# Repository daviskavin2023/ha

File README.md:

# 3038-网关-ha (Home Assistant 智能家居网关中心)

> 渔来喔智能家居体系核心网关。部署于 PVE 10 宿主机，通过 KVM 虚拟机运行 Home Assistant OS (HAOS)，实现对全屋开关、插座的集中管控、状态监控与高阶任务编排。

---

## 📌 项目定位

- **主控大脑**：Home Assistant 承担全屋逻辑控制、复杂任务编排、能源数据监控与跨协议桥接。
- **射频天线**：原**小米中枢网关**仅保留作为底层射频（Bluetooth Mesh / Zigbee）信号接收器，不参与任何上层自动化编排。
- **重点接管**：全屋智能开关（零火/单火、多键转无线）、智能计量插座（功率监测、电量统计）。

---

## 📁 目录结构

```text
3038-网关-ha/
├── PRD.md              # 产品与技术需求文档 (详细架构、避坑指南、配置规范)
├── README.md           # 项目速览与操作说明
└── docs/               # 部署命令、配置样例与自动化模板 (规划中)
```

---

## 🚀 核心架构与部署参数

- **宿主环境**：PVE 10 宿主机 (`10.10.10.10`)
- **虚拟机类型**：KVM (HAOS 官方 qcow2 镜像)
- **VM 规格**：
  - VM ID: `138` (名称: `haos-138`)
  - 固定 IP: `10.10.10.38/24`
  - 默认网关: `10.10.10.15` (旁路由)
  - DNS 服务器: `10.10.10.15` (旁路由)
  - BIOS: `OVMF (UEFI)`
  - Machine: `q35`
  - CPU: 2 vCPU (Type: `host`)
  - 内存: 4GB
  - 存储: 32GB ~ 64GB SSD (VirtIO SCSI Single, 开启 Discard)
  - 扩展特性: 开启 QEMU Guest Agent
- **访问端口**：
  - HA 原生 Web: `http://10.10.10.38:8123`
  - 渔来喔映射代号: `3038`

---

## 🛡️ 扫描与自检四项铁律（写死红线）

针对网关中心所有后台扫描、设备巡检、自动化自检与排查脚本，必须 100% 遵守以下规则（永久写死）：
1. **扫描的时候严禁触发回家，回家只允许物理按键**：全屋任何回家模式/欢迎联动只允许由实体物理按键触发，严禁任何扫描探针或脚本软件触发。
2. **扫描的时候严禁触发观影模式后又不恢复成功，搞得观影挂起**：严禁遗留观影模式，若临时测试必须通过 `try...finally` 100% 保证复位，绝不允许导致观影挂起死锁灯光。
3. **扫描的时候严禁触发空调**：巡检探针只读探测，严禁向全屋任何空调或温控下发任何控制指令，绝对不得影响空调运行。
4. **扫描前后的所有配置应该维持一样，严禁扫描完开了又忘记关、管理又忘记开**：严禁扫描完设备开了又忘记关；严禁排查时停用自动化/服务后管理又忘记开。

详细规划、技术避坑指南与实施步骤请参阅：[PRD.md](./PRD.md)。

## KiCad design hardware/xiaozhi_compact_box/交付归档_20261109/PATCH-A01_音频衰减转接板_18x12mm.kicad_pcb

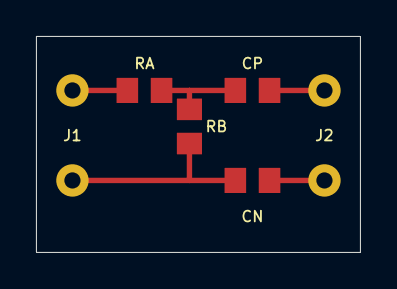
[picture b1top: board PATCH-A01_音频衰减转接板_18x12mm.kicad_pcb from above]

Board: 2 copper layers, 18.0 x 12.0 mm, 6 parts (0 on the bottom side), 5 nets.

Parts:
CN: 1uF_X7R_25V; smd
CP: 1uF_X7R_25V; smd
J1: WIRE_IN; wire
J2: WIRE_OUT; wire
RA: 15k_1pct; smd
RB: 1k_1pct; smdv

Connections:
AMP_IN_N_AC: CN.2, J2.2
AMP_IN_P_AC: CP.2, J2.1
ATTENUATED: CP.1, RA.2, RB.1
GND: CN.1, J1.2, RB.2
MIX_IN: J1.1, RA.1

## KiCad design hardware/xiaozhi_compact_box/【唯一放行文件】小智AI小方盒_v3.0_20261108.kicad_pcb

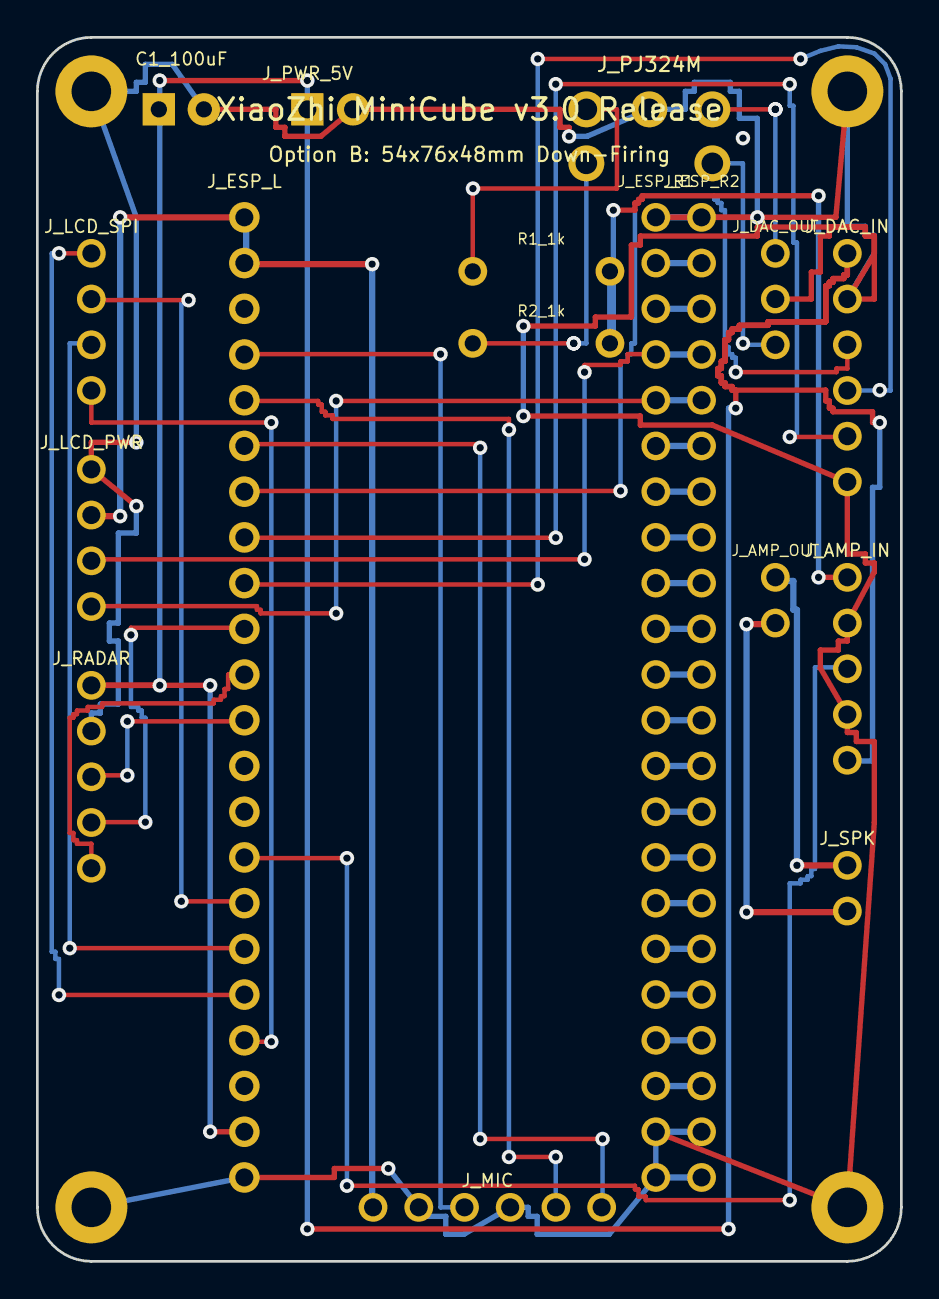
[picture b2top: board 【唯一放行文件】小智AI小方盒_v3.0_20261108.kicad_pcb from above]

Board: 2 copper layers, 48.0 x 68.0 mm, 17 parts (0 on the bottom side), 43 nets.

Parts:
C1_100uF: CP_Radial_D5.0mm_P2.50mm
J_AMP_IN: PinSocket_1x05_P2.54mm_Vertical
J_AMP_OUT: PinSocket_1x02_P2.54mm_Vertical
J_DAC_IN: PinSocket_1x06_P2.54mm_Vertical
J_DAC_OUT: PinSocket_1x03_P2.54mm_Vertical
J_ESP_L: PinSocket_1x22_P2.54mm_Vertical
J_ESP_R1, J_ESP_R2: PinSocket_1x22_P2.54mm_Vertical
J_LCD_PWR: PinSocket_1x04_P2.54mm_Vertical
J_LCD_SPI: PinSocket_1x04_P2.54mm_Vertical
J_MIC: PinSocket_1x06_P2.54mm_Vertical
J_PJ324M: Jack_3.5mm_PJ324M_Horizontal
J_PWR_5V: PinHeader_1x02_P2.54mm_Vertical
J_RADAR: PinSocket_1x05_P2.54mm_Vertical
J_SPK: PinHeader_1x02_P2.54mm_Vertical
R1_1k, R2_1k: R_Axial_DIN0207_L6.3mm_D2.5mm_P7.62mm_Horizontal

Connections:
+3V3: J_ESP_L.1, J_ESP_L.2, J_LCD_PWR.2, J_MIC.1
+5V: C1_100uF.1, J_AMP_IN.5, J_DAC_IN.1, J_ESP_L.21, J_PWR_5V.1, J_RADAR.1
AMP_IN_SIG: J_AMP_IN.1, R1_1k.2, R2_1k.2
AMP_SD_IO9: J_AMP_IN.3, J_ESP_L.15
AUDIO_L_OUT: J_DAC_OUT.1, J_PJ324M.2
AUDIO_R_OUT: J_DAC_OUT.3, J_PJ324M.4
DAC_BCK_IO7: J_DAC_IN.3, J_ESP_L.7
DAC_DIN_IO16: J_DAC_IN.4, J_ESP_L.9
DAC_LCK_IO15: J_DAC_IN.5, J_ESP_L.8
GND: C1_100uF.2, J_AMP_IN.2, J_AMP_IN.4, J_DAC_IN.2, J_DAC_IN.6, J_DAC_OUT.2, J_ESP_L.22, J_ESP_R1.1, J_ESP_R1.21, J_ESP_R1.22, J_ESP_R2.1, J_ESP_R2.21, J_ESP_R2.22, J_LCD_PWR.1, J_MIC.2, J_MIC.4, J_PJ324M.1, J_PWR_5V.2, J_RADAR.2
IO0: J_ESP_R1.14, J_ESP_R2.14
IO19: J_ESP_R1.20, J_ESP_R2.20
IO20: J_ESP_R1.19, J_ESP_R2.19
IO21: J_ESP_R1.18, J_ESP_R2.18
IO35: J_ESP_R1.13, J_ESP_R2.13
IO36: J_ESP_R1.12, J_ESP_R2.12
IO37: J_ESP_R1.11, J_ESP_R2.11
IO38: J_ESP_R1.10, J_ESP_R2.10
IO39: J_ESP_R1.9, J_ESP_R2.9
IO40: J_ESP_R1.8, J_ESP_R2.8
IO41: J_ESP_R1.7, J_ESP_R2.7
IO42: J_ESP_R1.6, J_ESP_R2.6
IO45: J_ESP_R1.15, J_ESP_R2.15
IO47: J_ESP_R1.17, J_ESP_R2.17
IO48: J_ESP_R1.16, J_ESP_R2.16
LCD_CS_IO13: J_ESP_L.19, J_LCD_SPI.4
LCD_DC_IO10: J_ESP_L.16, J_LCD_SPI.2
LCD_MOSI_IO12: J_ESP_L.18, J_LCD_SPI.1
LCD_SCK_IO11: J_ESP_L.17, J_LCD_SPI.3
MIC_SCK_IO6: J_ESP_L.6, J_MIC.6
MIC_SD_IO4: J_ESP_L.4, J_MIC.3
MIC_WS_IO5: J_ESP_L.5, J_MIC.5
RADAR_OUT_IO8: J_ESP_L.12, J_RADAR.3
RADAR_RX_IO17: J_ESP_L.10, J_RADAR.4
RADAR_TX_IO18: J_ESP_L.11, J_RADAR.5
RING_SW: J_PJ324M.5, R2_1k.1
RX: J_ESP_R1.3, J_ESP_R2.3
SPK_N: J_AMP_OUT.2, J_SPK.2
SPK_P: J_AMP_OUT.1, J_SPK.1
TIP_SW: J_PJ324M.3, R1_1k.1
TOUCH_SCL_IO1: J_ESP_R1.4, J_ESP_R2.4, J_LCD_PWR.3
TOUCH_SDA_IO2: J_ESP_R1.5, J_ESP_R2.5, J_LCD_PWR.4
TX: J_ESP_R1.2, J_ESP_R2.2

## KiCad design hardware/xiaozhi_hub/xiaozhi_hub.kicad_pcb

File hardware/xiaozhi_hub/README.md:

# 小智 AI 桌面中控完全体 · PCB 制造与装配手册 (v1.0 旗舰双模版)

## 一、交付文件清单

1. **嘉立创一键打样包**：
   - 本地路径: `/Users/kavin/Projects/yulaiwo/3038-网关-ha/hardware/xiaozhi_hub/Xiaozhi_Hub_JLCPCB_Order.zip`
   - 包含文件: `xiaozhi_hub.kicad_pcb` + `xiaozhi_pcb_assembly_guide.png`
2. **KiCad 原生设计文件** (嘉立创 / 立创EDA 100% 原生识别):
   - 本地路径: `/Users/kavin/Projects/yulaiwo/3038-网关-ha/hardware/xiaozhi_hub/xiaozhi_hub.kicad_pcb`
3. **超高清装配接线指南图**:
   - 本地路径: `/Users/kavin/Projects/yulaiwo/3038-网关-ha/hardware/xiaozhi_hub/xiaozhi_pcb_assembly_guide.png`

---

## 二、嘉立创 0 元免费打样步骤 (只需 1 分钟)

1. 打开浏览器进入 **[嘉立创官网 (jlc.com)](https://www.jlc.com)** 或打开 **嘉立创下单小助手** / 微信小程序。
2. 点击 **【PCB 下单】** -> 点击 **【上传 PCB / Gerber 文件】**。
3. 选择上传我为你生成的打样包:
   `Xiaozhi_Hub_JLCPCB_Order.zip` (或直接上传 `xiaozhi_hub.kicad_pcb`)。
4. 嘉立创系统会自动解析出长宽尺寸 (**80mm × 75mm**) 与层数 (**2 层板**)。
5. **打样参数推荐勾选**：
   - **板子数量**: 5 片 (默认)
   - **板子厚度**: 1.6mm (默认标准)
   - **阻焊颜色**: **哑光黑** (沉稳高级) 或 **紫色** (极客风)
   - **表面处理**: **有铅喷锡** 或 **沉金** (每月免费券支持免费打样)
6. 提交订单时勾选**【使用每月免费打样券】** -> 实付 **0 元顺丰包邮**！

---

## 三、立创 EDA 网页版导入查看 3D 图 (可选)

如果你想在刚才注册的 **[立创 EDA 网页 (lceda.cn)](https://lceda.cn)** 预览 3D 效果：
1. 点击顶部菜单 **【文件】 -> 【打开】 -> 【KiCad】**。
2. 选中并上传 `xiaozhi_hub.kicad_pcb`。
3. 点击菜单栏 **【视图】 -> 【3D 视图】**，即可在浏览器中 360 度立体旋转查看整块板子！

---

## 四、硬件引脚与模块功能速查表

| 模块名称 | 接口类型 | 对应 ESP32-S3 针脚 | 供电轨 | 关键作用与注意事项 |
| :--- | :--- | :--- | :--- | :--- |
| **主电源** | 2-Pin 5V / Type-C | 5V & GND (跨接 100µF 电容) | 5V 主轨 | 独立大铜皮供电，彻底杜绝短路倒灌 |
| **ESP32-S3** | 2×22P 双排母 | 标准 DevKitC 针脚 | 5V 受电 | **免焊 IN-OUT**，插上直接工作 |
| **2.01寸触控彩屏** | 2×4P 插座 | SPI: IO12, 10, 11, 13<br>I2C: IO1, IO2 | 3.3V 纯净轨 | ST7789 高亮动态大眼睛 + CST816 触摸 |
| **INMP441 麦克风** | 1×6P 单排母 | SD: IO4, WS: IO5, SCK: IO6 | 3.3V 纯净轨 | 前沿开孔拾音，L/R 接地选左声道 |
| **LD2410C 雷达** | 1×5P 单排母 | OUT: IO8, RX: IO17, TX: IO18 | 5V 主轨 | 人体存在感知，天线朝前/上方安装 |
| **PCM5102A 解码** | 1×6P+1×3P 排母 | BCK: IO7, DIN: IO16, LCK: IO15 | 5V 主轨 | 发烧级 I2S DAC，模拟地星型隔离 |
| **PAM8302A 功放** | 1×5P 排母 | A+: 音频信号, SD: IO9 | 5V 主轨 | TI 超低底噪功放，拔线后驱动喇叭 |
| **PJ-324M 接口** | 5-Pin 耳机座 | Pin1: AGND, Pin2: L, Pin3: R<br>Pin4/5: 机械断开开关触点 | 纯音频通路 | **插线 220V 音箱响，拔线小喇叭响** |
| **全频腔体喇叭** | 1×2P 插座 | VO+ / VO- | 来自功放 | 4Ω 3W/5W 带被动低音振膜腔体音箱 |

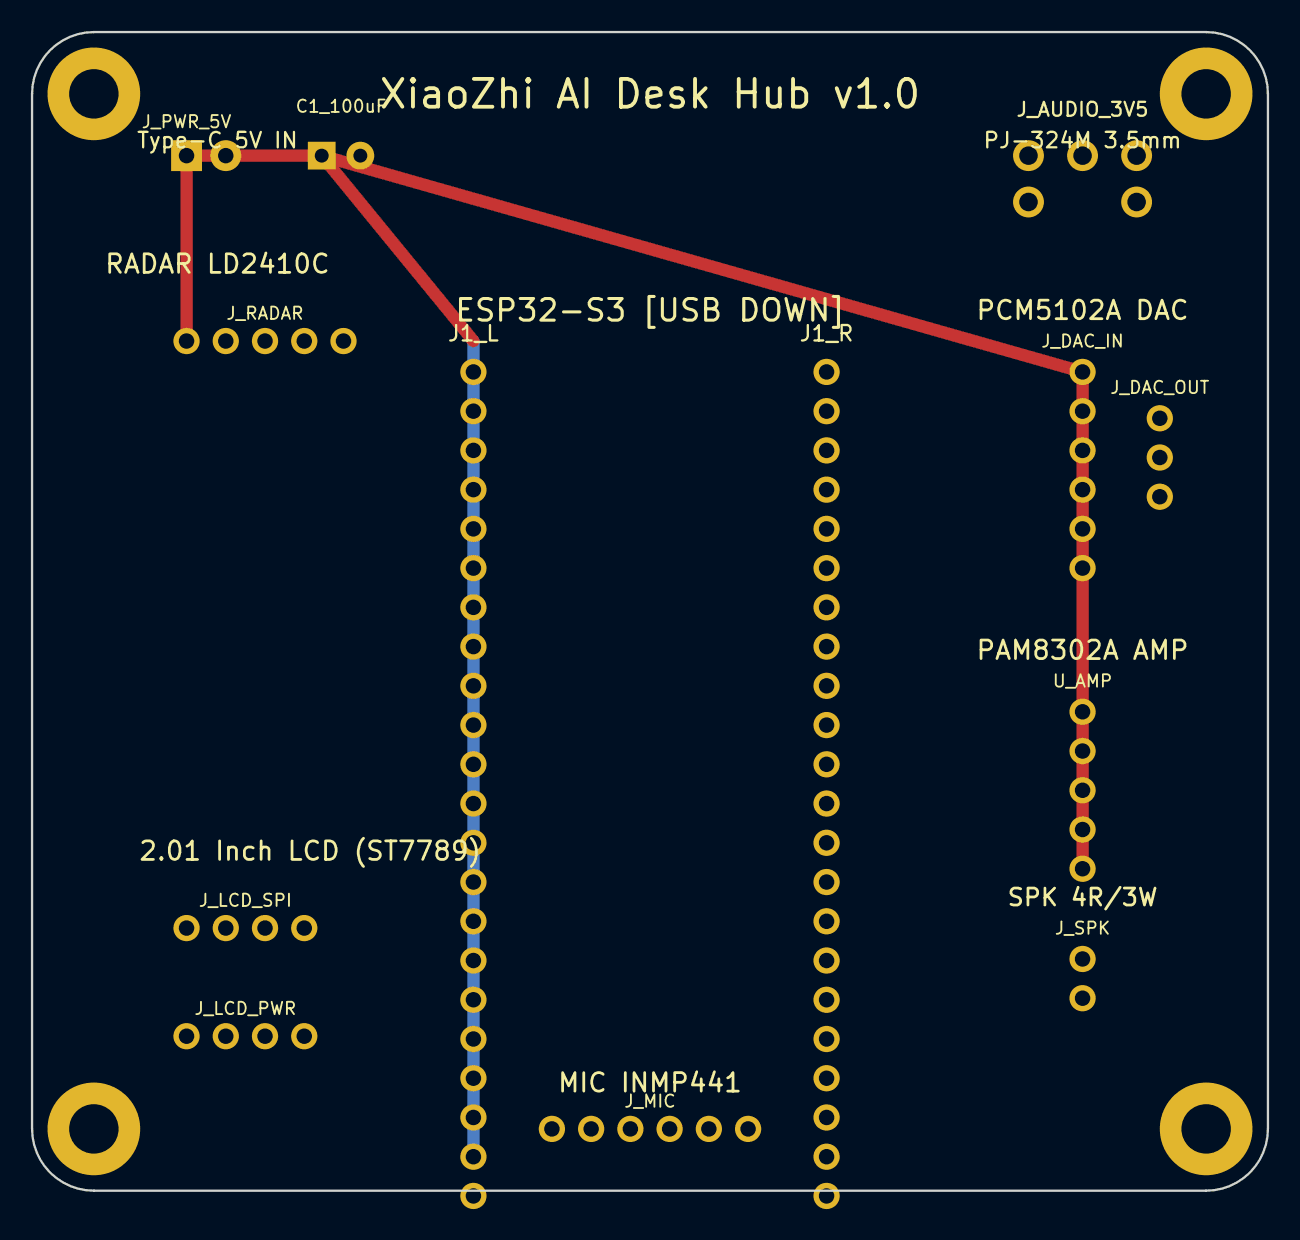
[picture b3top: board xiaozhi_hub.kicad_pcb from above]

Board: 2 copper layers, 80.0 x 75.0 mm, 13 parts (0 on the bottom side), 22 nets.

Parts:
C1_100uF: CP_Radial_D6.3mm_P2.50mm
J1_L, J1_R: PinSocket_1x22_P2.54mm_Vertical
J_AUDIO_3V5: Jack_3.5mm_PJ324M_Horizontal
J_DAC_IN: PinSocket_1x06_P2.54mm_Vertical
J_DAC_OUT: PinSocket_1x03_P2.54mm_Vertical
J_LCD_PWR: PinSocket_1x04_P2.54mm_Vertical
J_LCD_SPI: PinSocket_1x04_P2.54mm_Vertical
J_MIC: PinSocket_1x06_P2.54mm_Vertical
J_PWR_5V: PinHeader_1x02_P2.54mm_Vertical
J_RADAR: PinSocket_1x05_P2.54mm_Vertical
J_SPK: PinHeader_1x02_P2.54mm_Vertical
U_AMP: PinSocket_1x05_P2.54mm_Vertical

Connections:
+3V3: J1_L.1, J1_L.2, J_LCD_PWR.2, J_MIC.1
+5V: C1_100uF.1, J1_L.21, J_DAC_IN.1, J_PWR_5V.1, J_RADAR.1, U_AMP.5
AMP_IN_SIG: J_AUDIO_3V5.4, J_AUDIO_3V5.5, U_AMP.1
AMP_SD_IO9: J1_L.15, U_AMP.3
AUDIO_L_OUT: J_AUDIO_3V5.2, J_DAC_OUT.1
AUDIO_R_OUT: J_AUDIO_3V5.3, J_DAC_OUT.3
DAC_BCK_IO7: J1_L.7, J_DAC_IN.3
DAC_DIN_IO16: J1_L.9, J_DAC_IN.4
DAC_LCK_IO15: J1_L.8, J_DAC_IN.5
GND: C1_100uF.2, J1_L.22, J1_R.1, J1_R.21, J1_R.22, J_AUDIO_3V5.1, J_DAC_IN.2, J_DAC_IN.6, J_DAC_OUT.2, J_LCD_PWR.1, J_MIC.2, J_MIC.4, J_PWR_5V.2, J_RADAR.2, U_AMP.2, U_AMP.4
LCD_CS_IO13: J1_L.19, J_LCD_SPI.4
LCD_DC_IO10: J1_L.16, J_LCD_SPI.2
LCD_MOSI_IO12: J1_L.18, J_LCD_SPI.1
LCD_SCK_IO11: J1_L.17, J_LCD_SPI.3
MIC_SCK_IO6: J1_L.6, J_MIC.6
MIC_SD_IO4: J1_L.4, J_MIC.3
MIC_WS_IO5: J1_L.5, J_MIC.5
RADAR_OUT_IO8: J1_L.12, J_RADAR.3
RADAR_RX_IO17: J1_L.10, J_RADAR.4
RADAR_TX_IO18: J1_L.11, J_RADAR.5
TOUCH_SCL_IO1: J1_R.4, J_LCD_PWR.3
TOUCH_SDA_IO2: J1_R.5, J_LCD_PWR.4

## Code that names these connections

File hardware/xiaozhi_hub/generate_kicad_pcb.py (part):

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    # At (35, 71)
    # Pin 1: VDD(3V3), 2: GND, 3: SD, 4: L/R(GND), 5: WS, 6: SCK
    # ==========================================
    mic_pins = [(3, "+3V3"), (1, "GND"), (4, "MIC_SD_IO4"), (1, "GND"), (5, "MIC_WS_IO5"), (6, "MIC_SCK_IO6")]
    pcb_content += """  (footprint "Connector_PinSocket_2.54mm:PinSocket_1x06_P2.54mm_Vertical" (layer "F.Cu")
    (at 33.65 71)
    (fp_text reference "J_MIC" (at 6.35 -1.8) (layer "F.SilkS") (effects (font (size 0.8 0.8) (thickness 0.12))))
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    # At (10, 20)
    # Pin 1: 5V, 2: GND, 3: OUT, 4: TX, 5: RX
    # ==========================================
    radar_pins = [(2, "+5V"), (1, "GND"), (8, "RADAR_OUT_IO8"), (16, "RADAR_RX_IO17"), (17, "RADAR_TX_IO18")]
    pcb_content += """  (footprint "Connector_PinSocket_2.54mm:PinSocket_1x05_P2.54mm_Vertical" (layer "F.Cu")
    (at 10 20)
    (fp_text reference "J_RADAR" (at 5.08 -1.8) (layer "F.SilkS") (effects (font (size 0.8 0.8) (thickness 0.12))))
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    # ==========================================
    # U1: PAM8302A Amp Socket (1x5 2.54mm)
    # At (68, 44)
    # Pin 1: A+(AMP_IN_SIG), 2: A-(GND), 3: SD(AMP_SD), 4: GND, 5: 5V
    # ==========================================
    amp_pins = [(22, "AMP_IN_SIG"), (1, "GND"), (9, "AMP_SD_IO9"), (1, "GND"), (2, "+5V")]
    pcb_content += """  (footprint "Connector_PinSocket_2.54mm:PinSocket_1x05_P2.54mm_Vertical" (layer "F.Cu")
    (at 68 44)
    (fp_text reference "U_AMP" (at 0 -2.0) (layer "F.SilkS") (effects (font (size 0.8 0.8) (thickness 0.12))))
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    # J8: Speaker Header (1x2 2.54mm / XH2.54)
    # At (68, 60)
    # ==========================================
    spk_pins = [(23, "SPK_P"), (24, "SPK_N")]
    pcb_content += """  (footprint "Connector_PinHeader_2.54mm:PinHeader_1x02_P2.54mm_Vertical" (layer "F.Cu")
    (at 68 60)
    (fp_text reference "J_SPK" (at 0 -2.0) (layer "F.SilkS") (effects (font (size 0.8 0.8) (thickness 0.12))))
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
